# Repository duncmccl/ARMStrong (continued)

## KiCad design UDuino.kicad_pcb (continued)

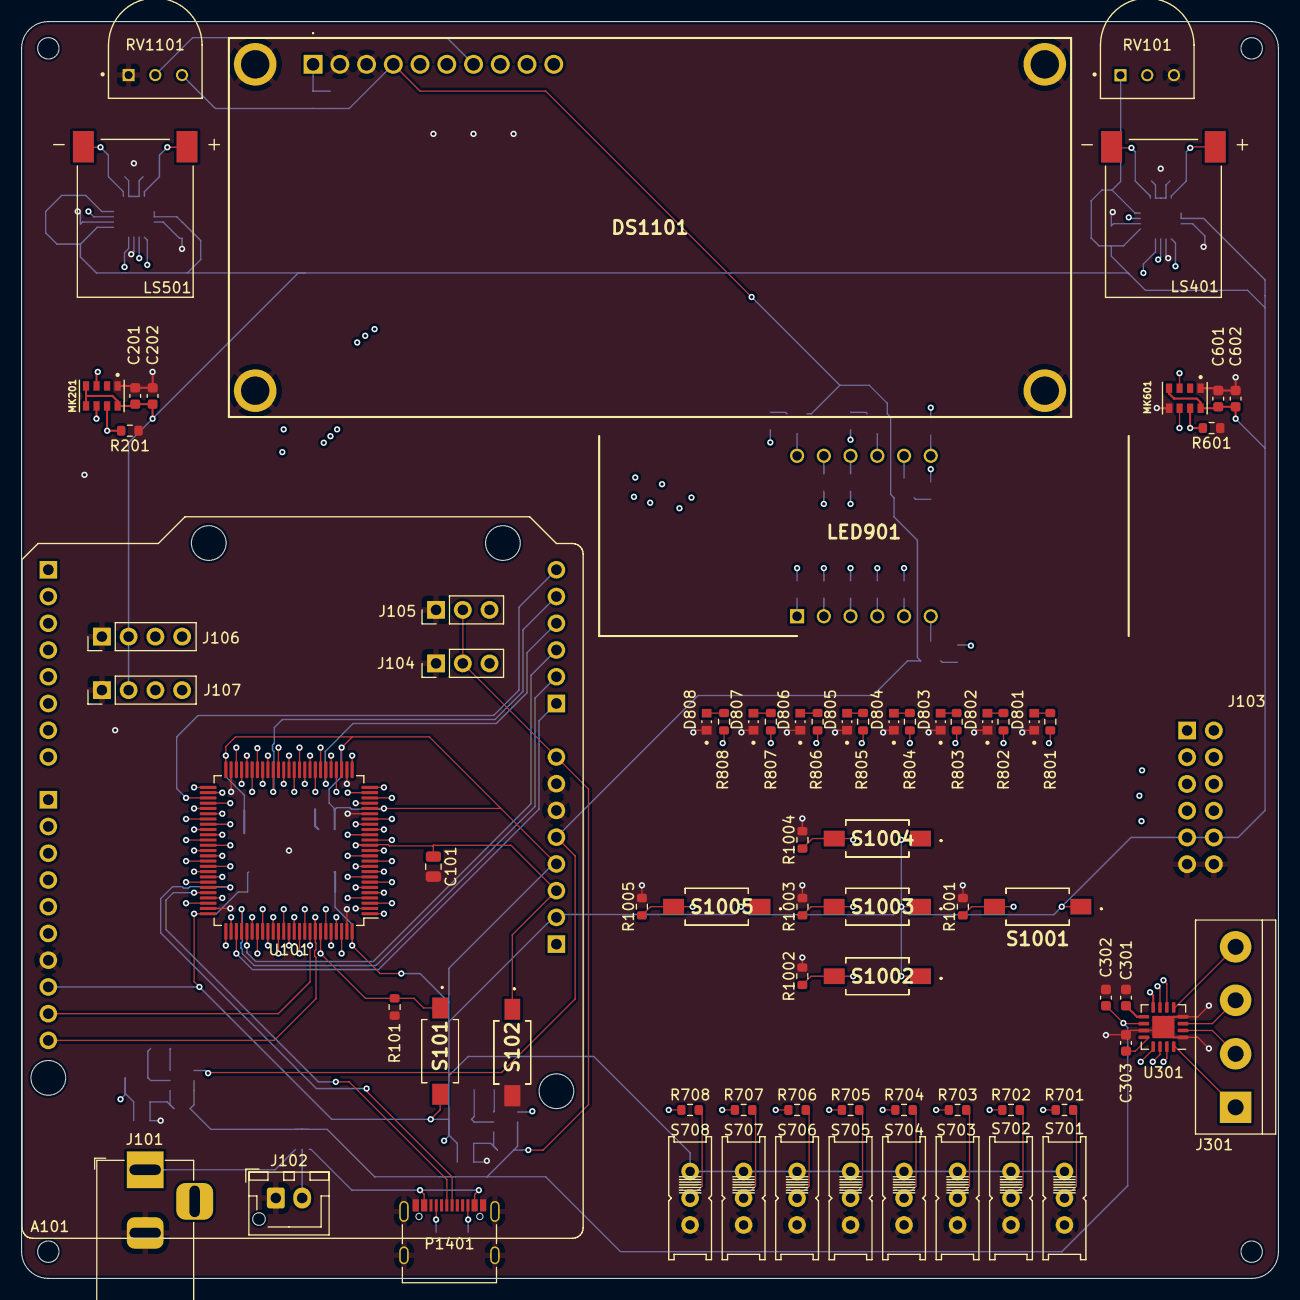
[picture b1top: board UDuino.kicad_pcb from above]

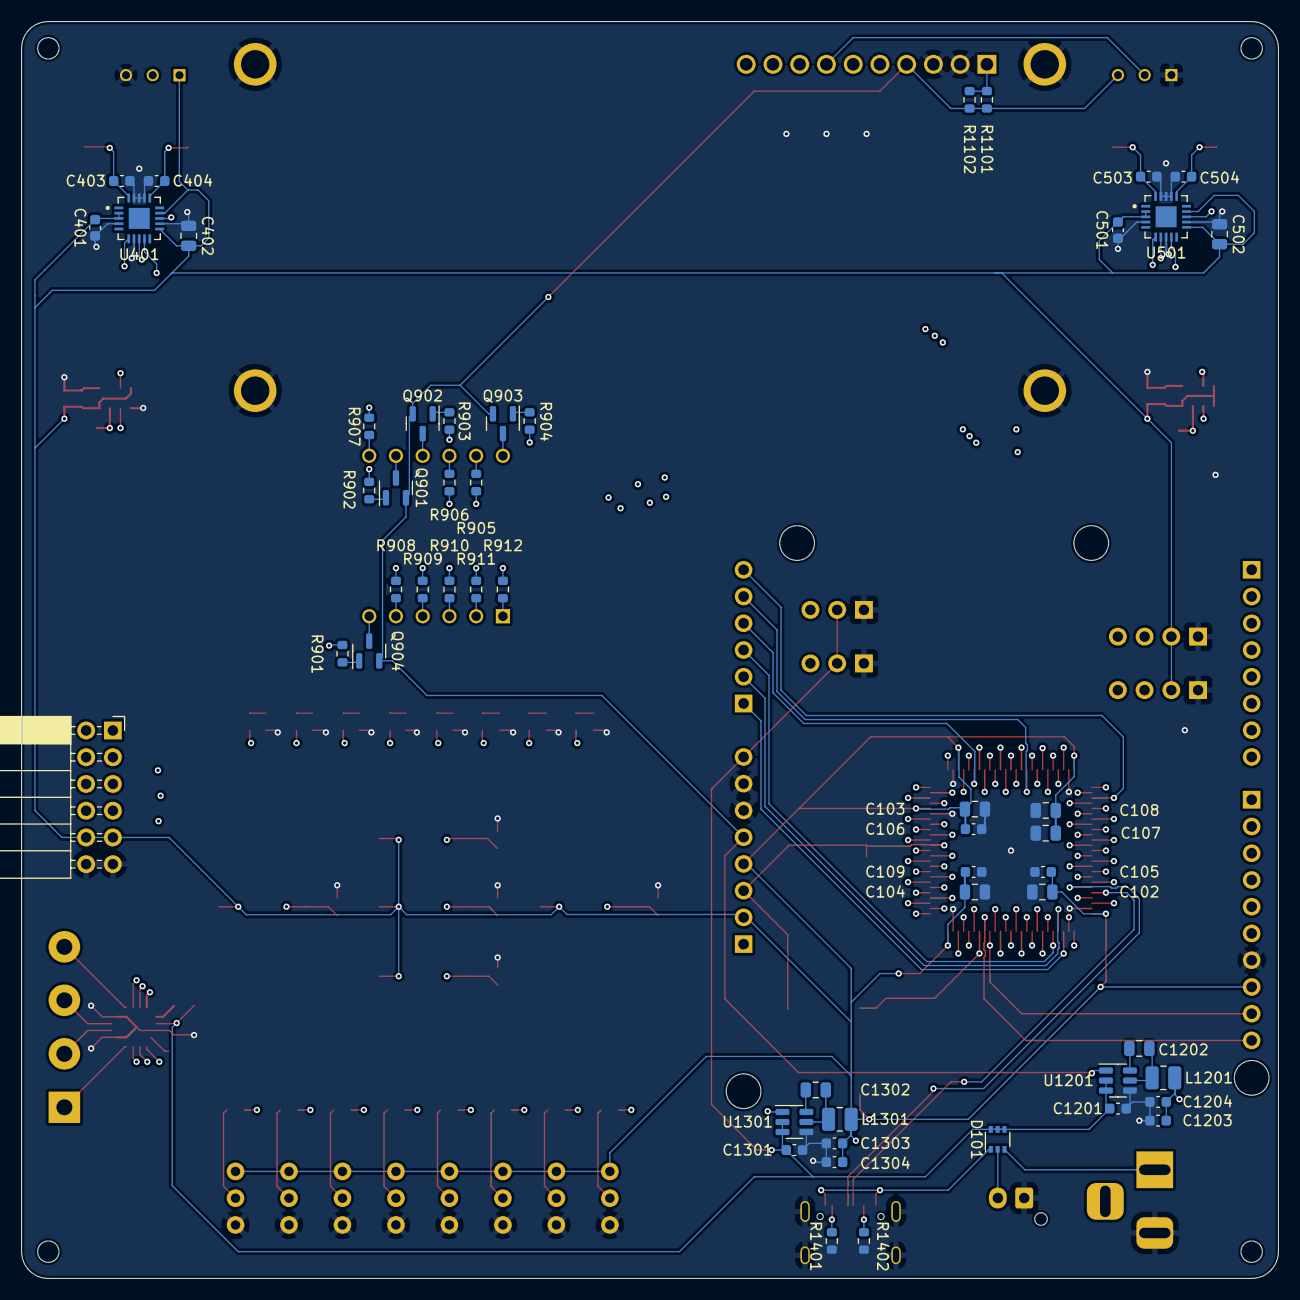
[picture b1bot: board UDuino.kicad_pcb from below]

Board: 4 copper layers, 119.4 x 119.4 mm, 126 parts (52 on the bottom side), 141 nets.

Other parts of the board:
C201: 10u; C_0603_1608Metric
C202: 10n; C_0603_1608Metric
C501: 4u7; C_0603_1608Metric
C502: 100n; C_0805_2012Metric
C503, C504: 1n; C_0603_1608Metric
LS501: Speaker; SPKR_AS01508MS-SC11-WP-R
MK201: CMM-4030D-261-I2S-TR; MIC_CMM-4030D-261-I2S-TR
R201: 100; R_0603_1608Metric
U501: NAU8315YG; QFN50P400X400X80-21N

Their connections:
+3V3: C201.1, C202.2, C501.2, C502.1, MK201.4 (CHIPEN), MK201.5 (L/R), MK201.8 (VDD), U501.2 (VDD), U501.3 (EN), U501.11 (VDD), U501.14 (VDD); also elsewhere on the board
/I2S1_CK: U501.6 (BCLK); also elsewhere on the board
/I2S1_SD: U501.9 (DACIN); also elsewhere on the board
/I2S1_WS: U501.7 (FSR); also elsewhere on the board
/I2S2_CK: MK201.6 (SCK); also elsewhere on the board
/I2S2_SD: MK201.7 (SD), R201.2; also elsewhere on the board
/I2S2_WS: MK201.3 (WS); also elsewhere on the board
/Speaker Left/GAIN: U501.13 (GAIN); also elsewhere on the board
GND: C201.2, C202.1, C501.1, C502.2, C503.1, C504.2, MK201.1 (GND), R201.1, U501.4 (GND), U501.8 (FSL), U501.12 (GND), U501.17 (GND), U501.18 (GND), U501.19 (GND); also elsewhere on the board
unnamed: C503.2, LS501.P (1), U501.20 (OUTP)
unnamed: C504.1, LS501.N (2), U501.16 (OUTN)

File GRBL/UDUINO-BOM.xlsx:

Comment | Designator | Footprint | Manufacturer | Manufacturer Part Number
A000066 | A101 | Custom:ARDUINO_A000066 | Arduino | A000066
100n | C101, C102, C103, C104, C107, C108, C402, C502, C1202, C1302 | Capacitor_SMD:C_0805_2012Metric | Samsung Electro-Mechanics | CL21B104KCFNNNE
4u7 | C105, C106, C109, C401, C501 | Capacitor_SMD:C_0603_1608Metric | Samsung Electro-Mechanics | CL10A475KO8NNNC
10u | C201, C302, C601, C1201, C1301 | Capacitor_SMD:C_0603_1608Metric | Samsung Electro-Mechanics | CL10A106KP8NNNC
10n | C202, C301, C602 | Capacitor_SMD:C_0603_1608Metric | Samsung Electro-Mechanics | 0603B103K500NT
2u2 | C303 | Capacitor_SMD:C_0603_1608Metric | Samsung Electro-Mechanics | CL10A225KO8NNNC
1n | C403, C404, C503, C504 | Capacitor_SMD:C_0603_1608Metric | Samsung Electro-Mechanics | CL10B102KB8NNNC
22u | C1203, C1204, C1303, C1304 | Capacitor_SMD:C_0603_1608Metric | Samsung Electro-Mechanics | CL10A226MQ8NRNC
BAS70TW | D101 | Package_TO_SOT_SMD:SOT-363_SC-70-6 | Diodes Incorporated | BAS70TW
LTST-C190KRKT | D801, D802, D803, D804, D805, D806, D807, D808 | LEDC1608X35N | Lite-On | LTST-C190KRKT
AMC1602AR-B-Y6WFDY-SPI | DS1101 | Custom:AMC1602ARBY6WFDYSPI | Orient Display | AMC1602AR-B-Y6WFDY-SPI
Barrel_Jack | J101 | Connector_BarrelJack:BarrelJack_Horizontal | GlobTek, Inc. | G-1005B
Conn_01x02_Female | J102 | Connector_JST:JST_XH_B2B-XH-AM_1x02_P2.50mm_Vertical
PMOD1 | J103 | Connector_PinSocket_2.54mm:PinSocket_2x06_P2.54mm_Horizontal
Conn_01x03_Male | J104, J105 | Connector_PinHeader_2.54mm:PinHeader_1x03_P2.54mm_Vertical
Conn_01x04_Male | J106, J107 | Connector_PinHeader_2.54mm:PinHeader_1x04_P2.54mm_Vertical
Screw_Terminal_01x04 | J301 | TerminalBlock:TerminalBlock_bornier-4_P5.08mm
4u7 | L1201, L1301 | Inductor_SMD:L_1008_2520Metric | Samsung Electro-Mechanics | CIGW252010GL4R7MNE
LDQ-M516RI | LED901 | Custom:DIPS1524W50P254L5030H800Q12N | Lumex Opto/Components Inc. | 67-1449-ND
Speaker | LS401, LS501 | Custom:SPKR_AS01508MS-SC11-WP-R | PUI Audio, Inc. | AS01508MS-SC11-WP-R
CMM-4030D-261-I2S-TR | MK201, MK601 | Custom:MIC_CMM-4030D-261-I2S-TR | CUI Devices | CMM-4030D-261-I2S-TR
USB4105-GF-A | P1401 | Connector_USB:USB_C_Receptacle_Palconn_UTC16-G
SMMBT4403LT1G | Q901, Q902, Q903, Q904 | Package_TO_SOT_SMD:SOT-23 | onsemi | SMMBT4403LT1G
10k | R101, R701, R702, R703, R704, R705, R706, R707, R708, R1001, R1002, R1003, R100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 | Resistor_SMD:R_0603_1608Metric | UNI-ROYAL(Uniroyal Elec) | 0603WAF1002T5E
100 | R201, R601, R1101, R1102 | Resistor_SMD:R_0603_1608Metric | UNI-ROYAL(Uniroyal Elec) | 0603WAF1000T5E
220 | R801, R802, R803, R804, R805, R806, R807, R808, R905, R906, R907, R908, R909, R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 | Resistor_SMD:R_0603_1608Metric | UNI-ROYAL(Uniroyal Elec) | 0603WAF2200T5E
1k | R901, R902, R903, R904 | Resistor_SMD:R_0603_1608Metric | UNI-ROYAL(Uniroyal Elec) | 0603WAF1001T5E
5k1 | R1401, R1402 | Resistor_SMD:R_0603_1608Metric | UNI-ROYAL(Uniroyal Elec) | 0603WAF5101T5E
100k | RV101, RV1101 | Custom:TRIM_3352T-1-104LF | Bourns Inc. | 3352T-1-104LF
PTS636 SM43 SMTR LFS | S101, S102, S1002, S1003, S1004, S1005 | PTS636SM43SMTRLFS | C & K COMPONENTS | PTS636 SM43 SMTR LFS
EG1218 | S701, S702, S703, S704, S705, S706, S707, S708 | EG1218 | E-Switch | EG1218
PTS636_SM43_SMTR_LFS | S1001 | Custom:PTS636SM43SMTRLFS | C & K COMPONENTS | PTS636 SM43 SMTR LFS
STM32F072VBTx | U101 | Package_QFP:LQFP-100_14x14mm_P0.5mm | STMicroelectronics | STM32F072VBT6
DRV8833RTY | U301 | Package_DFN_QFN:Texas_S-PWQFN-N16_EP2.1x2.1mm | Texas Instruments | DRV8833RTYT
NAU8315YG | U401, U501 | Custom:QFN50P400X400X80-21N | Nuvoton Technology Corporation | NAU8315YG
AP63205WU | U1201 | Package_TO_SOT_SMD:TSOT-23-6 | Diodes Incorporated | AP63205WU-7
AP63203WU | U1301 | Package_TO_SOT_SMD:TSOT-23-6 | Diodes Incorporated | AP63203WU-7

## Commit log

2022-10-25 Added Block diagram to README
2022-10-25 Update README
    Changed like to block diagram to higher resolution.
2022-10-27 Downloaded datasheets and EAGLE libraries.
2022-11-01 Reorganizeing files
2022-11-01 Reorganizing Files
2022-11-01 Added ESP32-S3 files
2022-11-03 LCD Eagle Library
2022-11-15 Changed project to use KiCAD
2022-11-15 Cleanup files
2022-11-15 Rough placement of Speakers on board
2022-11-15 Rough placement of the Motor controller
2022-11-16 Added Switches, Buttons, LEDs, 7Seg, LCD
2022-11-17 Update board design
    5v and 3v3 power blocks wired up.
2022-11-18 ARMStrong
2022-12-01 Routing of some wires
2022-12-06 06/12/2022
2023-02-10 First week after winter break. Changed Power circuit design to use different DC to DC converter Setting correct footprints for the components like resistors and capacitors.
2023-02-13 Weekend progress
    Things that remain:
    4 LEDs to Microcontroller
    7-Seg to Microcontroller
    LCD to Microcontroller
    Microphone and Speakers to Microcontroller
    Power circuitry
2023-02-16 Feb 12 2023 Week Work
    Remaining Things to accomplish
    Audio connect to Microcontroller
    7-Seg connect to Microcontroller
    PMOD connect to Microcontroller
    Misc Microcontroller items, like reset and boot buttons
2023-02-20 REVISION 0 DONE
    Done first revision of the UDUINO
2023-02-20 DRC checks done, GRBL files made
2023-02-20 Silk screen touch up
2023-02-20 Update BOM and POC files
2023-02-22 Fixed BOM and Silkscreen things
2023-02-22 Fixed mounting hole sizes
2023-04-15 Fixed 7seg display
